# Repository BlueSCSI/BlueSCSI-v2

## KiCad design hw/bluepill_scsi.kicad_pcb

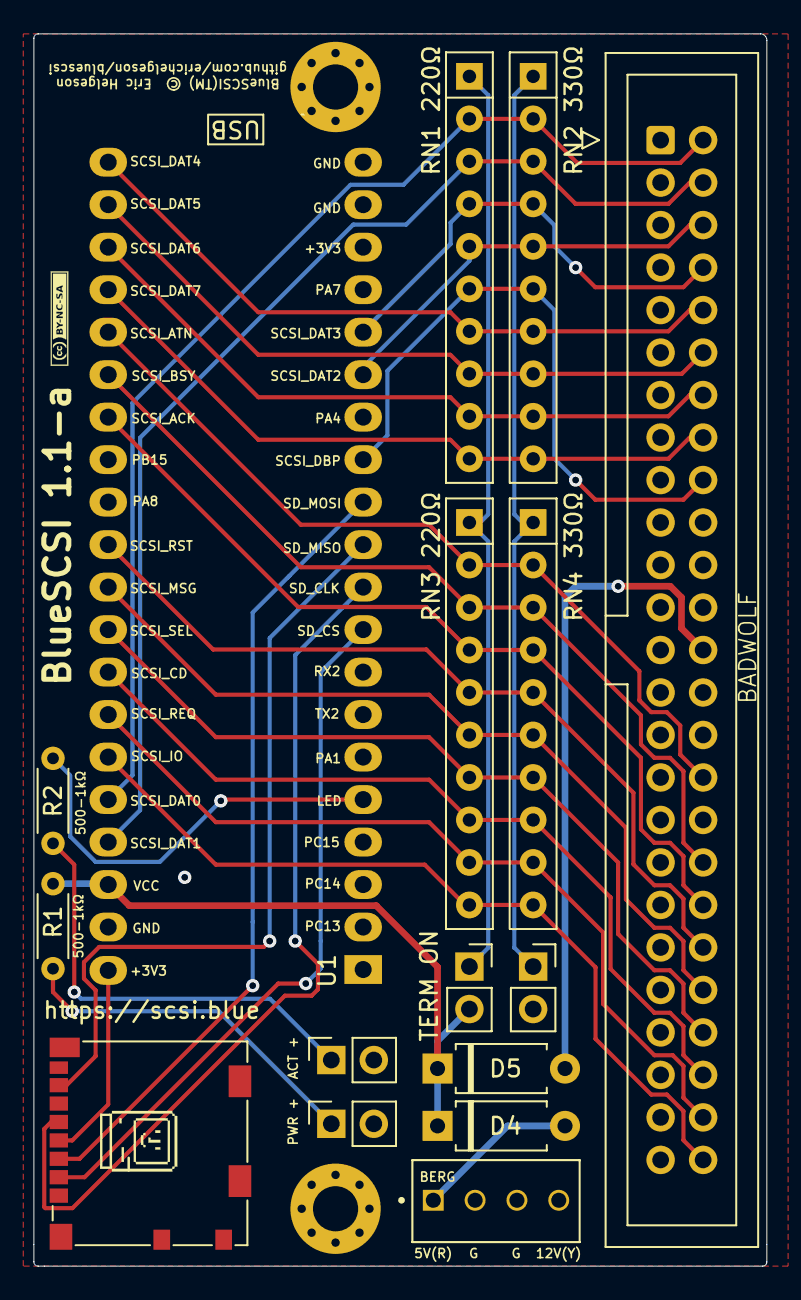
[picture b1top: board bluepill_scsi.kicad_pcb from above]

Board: 2 copper layers, 43.8 x 73.7 mm, 18 parts (0 on the bottom side), 32 nets.

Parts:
D4, D5: Diode; D_A-405_P7.62mm_Horizontal
H1, H2: MountingHole_Pad; MountingHole_2.7mm_M2.5_Pad_Via
J1: Berg Power Connector; TE_171825-4
J2: Conn_02x25_Odd_Even; IDC-Header_2x25_P2.54mm_Vertical
J3: ACT_LED; PinSocket_1x02_P2.54mm_Vertical
J4: POWER_LED; PinSocket_1x02_P2.54mm_Vertical
J5: Micro_SD_Card; microSD_HC_Molex_104031-0811
JP1: TERM_ENABLE_GND; PinSocket_1x02_P2.54mm_Vertical
JP2: TERM_ENABLE_5V; PinSocket_1x02_P2.54mm_Vertical
R1, R2: R_US; R_Axial_DIN0204_L3.6mm_D1.6mm_P5.08mm_Horizontal
RN1, RN3: 220; R_Array_SIP10
RN2, RN4: 330; R_Array_SIP10
U1: BluePill_STM32F103C

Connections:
+3V3: J5.4, U1.18, U1.40
+5V: D4.2, J1.1
/EXTERNAL_LED: R2.2, U1.5
/SCSI_ACK: J2.38, RN3.4, RN4.4, U1.27
/SCSI_ATN: J2.32, RN3.2, RN4.2, U1.25
/SCSI_BSY: J2.36, RN3.3, RN4.3, U1.26
/SCSI_CD: J2.46, RN3.8, RN4.8, U1.33
/SCSI_DAT0: J2.2, RN1.2, RN2.2, U1.36
/SCSI_DAT1: J2.4, RN1.3, RN2.3, U1.37
/SCSI_DAT2: J2.6, RN1.5, RN2.5, U1.15
/SCSI_DAT3: J2.8, RN1.4, RN2.4, U1.16
/SCSI_DAT4: J2.10, RN1.7, RN2.7, U1.21
/SCSI_DAT5: J2.12, RN1.8, RN2.8, U1.22
/SCSI_DAT6: J2.14, RN1.9, RN2.9, U1.23
/SCSI_DAT7: J2.16, RN1.10, RN2.10, U1.24
/SCSI_DBP: J2.18, RN1.6, RN2.6, U1.13
/SCSI_IO: J2.50, RN3.10, RN4.10, U1.35
/SCSI_MSG: J2.42, RN3.6, RN4.6, U1.31
/SCSI_REQ: J2.48, RN3.9, RN4.9, U1.34
/SCSI_RST: J2.40, RN3.5, RN4.5, U1.30
/SCSI_SEL: J2.44, RN3.7, RN4.7, U1.32
/SD_CLK: J5.5, U1.10
/SD_CS: J5.2, U1.9
/SD_MISO: J5.7, U1.11
/SD_MOSI: J5.3, U1.12
/TERM_PWR: D5.2, J2.26
GND: J1.2, J2.1, J2.3, J2.5, J2.7, J2.9, J2.11, J2.13, J2.15, J2.17, J2.19, J2.20, J2.21, J2.22, J2.23, J2.24, J2.27, J2.28, J2.29, J2.30, J2.31, J2.33, J2.35, J2.37, J2.39, J2.41, J2.43, J2.45, J2.47, J2.49, J3.2, J4.2, J5.6, J5.9, JP1.2, U1.19, U1.20, U1.39
unnamed: J3.1, R2.1
unnamed: J4.1, R1.1
unnamed: JP1.1, RN2.1, RN4.1
unnamed: JP2.1, RN1.1, RN3.1
VCC: D4.1, D5.1, JP2.2, R1.2, U1.38

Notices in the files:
hw/bluepill_scsi.kicad_pcb:
BlueSCSI(TM) © Eric Helgeson https://github.com/erichelgeson/bluescsi
